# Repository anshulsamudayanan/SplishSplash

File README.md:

# SplishSplash
A graffiti inspired split keyboard with a ergonomic design
I wanted to create a mentally soothing and satifying keyboard so it will be equipped with some nice keyswitches like the holypanda and nice foam inside to get that thock
Cart pictures are attached below

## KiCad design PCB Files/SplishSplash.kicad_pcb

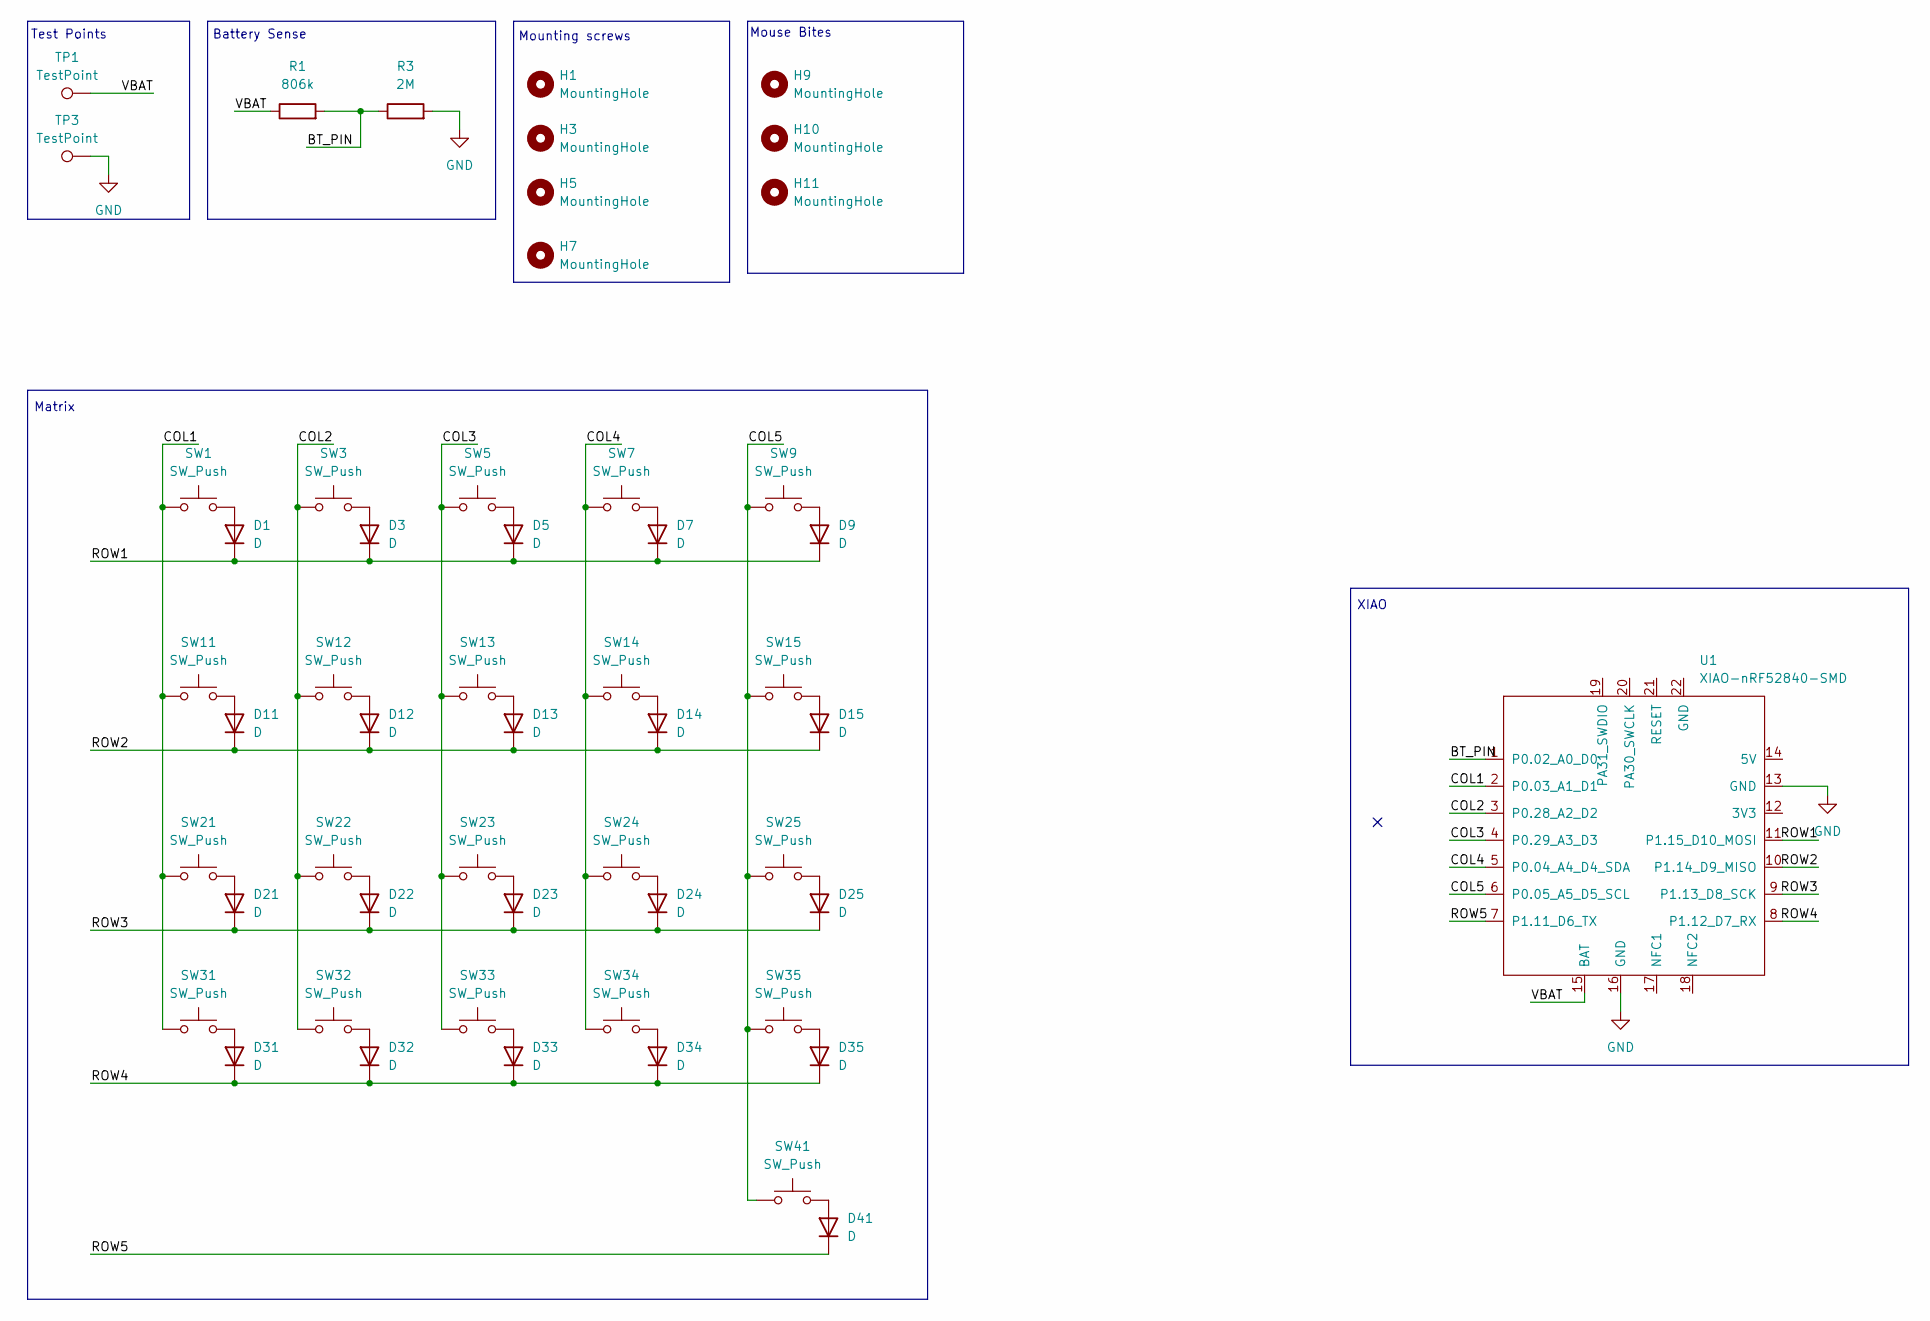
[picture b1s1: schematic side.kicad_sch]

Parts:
D1, D3, D5, D7, D9, D11, D12, D13, D14, D15, D21, D22, D23, D24, D25, D31, D32, D33, D34, D35, D41: D; D_SOD-123
H1, H3, H5, H7: MountingHole; MountingHole_2.2mm_M2
H9, H10, H11: MountingHole; mouse-bite-5mm-slot
R1: 806k; R_0805_2012Metric
R3: 2M; R_0805_2012Metric
SW1, SW3, SW5, SW7, SW9, SW11, SW12, SW13, SW14, SW15, SW21, SW22, SW23, SW24, SW25, SW31, SW32, SW33, SW34, SW35, SW41: SW_Push; SW_MX_HS_CPG151101S11_1u
TP1, TP3: TestPoint; TestPoint_Pad_D2.0mm
U1: XIAO-nRF52840-SMD; modified-XIAO-nRF52840-SMD

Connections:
/Left/BT_PIN: R1.2, R3.1, U1.1 (P0.02_A0_D0)
/Left/COL1: SW1.1, SW11.1, SW21.1, SW31.1, U1.2 (P0.03_A1_D1)
/Left/COL2: SW3.1, SW12.1, SW22.1, SW32.1, U1.3 (P0.28_A2_D2)
/Left/COL3: SW5.1, SW13.1, SW23.1, SW33.1, U1.4 (P0.29_A3_D3)
/Left/COL4: SW7.1, SW14.1, SW24.1, SW34.1, U1.5 (P0.04_A4_D4_SDA)
/Left/COL5: SW9.1, SW15.1, SW25.1, SW35.1, SW41.1, U1.6 (P0.05_A5_D5_SCL)
/Left/ROW1: D1.1 (K), D3.1 (K), D5.1 (K), D7.1 (K), D9.1 (K), U1.11 (P1.15_D10_MOSI)
/Left/ROW2: D11.1 (K), D12.1 (K), D13.1 (K), D14.1 (K), D15.1 (K), U1.10 (P1.14_D9_MISO)
/Left/ROW3: D21.1 (K), D22.1 (K), D23.1 (K), D24.1 (K), D25.1 (K), U1.9 (P1.13_D8_SCK)
/Left/ROW4: D31.1 (K), D32.1 (K), D33.1 (K), D34.1 (K), D35.1 (K), U1.8 (P1.12_D7_RX)
/Left/ROW5: D41.1 (K), U1.7 (P1.11_D6_TX)
/Left/VBAT: R1.1, TP1.1, U1.15 (BAT)
GND: R3.2, TP3.1, U1.13 (GND), U1.16 (GND); also elsewhere on the board
unnamed: D1.2 (A), SW1.2
unnamed: D3.2 (A), SW3.2
unnamed: D5.2 (A), SW5.2
unnamed: D7.2 (A), SW7.2
unnamed: D9.2 (A), SW9.2
unnamed: D11.2 (A), SW11.2
unnamed: D12.2 (A), SW12.2
unnamed: D13.2 (A), SW13.2
unnamed: D14.2 (A), SW14.2
unnamed: D15.2 (A), SW15.2
unnamed: D21.2 (A), SW21.2
unnamed: D22.2 (A), SW22.2
unnamed: D23.2 (A), SW23.2
unnamed: D24.2 (A), SW24.2
unnamed: D25.2 (A), SW25.2
unnamed: D31.2 (A), SW31.2
unnamed: D32.2 (A), SW32.2
unnamed: D33.2 (A), SW33.2
unnamed: D34.2 (A), SW34.2
unnamed: D35.2 (A), SW35.2
unnamed: D41.2 (A), SW41.2

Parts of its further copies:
D2, D4, D6, D8, D10, D16, D17, D18, D19, D20, D26, D27, D28, D29, D30, D36, D37, D38, D39, D40, D42: D; D_SOD-123
H2, H4, H6, H8: MountingHole; MountingHole_2.2mm_M2
R2: 806k; R_0805_2012Metric
R4: 2M; R_0805_2012Metric
SW2, SW4, SW6, SW8, SW10, SW16, SW17, SW18, SW19, SW20, SW26, SW27, SW28, SW29, SW30, SW36, SW37, SW38, SW39, SW40, SW42: SW_Push; SW_MX_HS_CPG151101S11_1u
TP2, TP4: TestPoint; TestPoint_Pad_D2.0mm
U2: XIAO-nRF52840-SMD; modified-XIAO-nRF52840-SMD

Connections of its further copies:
/Right/BT_PIN: R2.2, R4.1, U2.1 (P0.02_A0_D0)
/Right/COL1: SW2.1, SW16.1, SW26.1, SW36.1, U2.2 (P0.03_A1_D1)
/Right/COL2: SW4.1, SW17.1, SW27.1, SW37.1, U2.3 (P0.28_A2_D2)
/Right/COL3: SW6.1, SW18.1, SW28.1, SW38.1, U2.4 (P0.29_A3_D3)
/Right/COL4: SW8.1, SW19.1, SW29.1, SW39.1, U2.5 (P0.04_A4_D4_SDA)
/Right/COL5: SW10.1, SW20.1, SW30.1, SW40.1, SW42.1, U2.6 (P0.05_A5_D5_SCL)
/Right/ROW1: D2.1 (K), D4.1 (K), D6.1 (K), D8.1 (K), D10.1 (K), U2.11 (P1.15_D10_MOSI)
/Right/ROW2: D16.1 (K), D17.1 (K), D18.1 (K), D19.1 (K), D20.1 (K), U2.10 (P1.14_D9_MISO)
/Right/ROW3: D26.1 (K), D27.1 (K), D28.1 (K), D29.1 (K), D30.1 (K), U2.9 (P1.13_D8_SCK)
/Right/ROW4: D36.1 (K), D37.1 (K), D38.1 (K), D39.1 (K), D40.1 (K), U2.8 (P1.12_D7_RX)
/Right/ROW5: D42.1 (K), U2.7 (P1.11_D6_TX)
/Right/VBAT: R2.1, TP2.1, U2.15 (BAT)
GND: R4.2, TP4.1, U2.13 (GND), U2.16 (GND); also elsewhere on the board
unnamed: D2.2 (A), SW2.2
unnamed: D4.2 (A), SW4.2
unnamed: D6.2 (A), SW6.2
unnamed: D8.2 (A), SW8.2
unnamed: D10.2 (A), SW10.2
unnamed: D16.2 (A), SW16.2
unnamed: D17.2 (A), SW17.2
unnamed: D18.2 (A), SW18.2
unnamed: D19.2 (A), SW19.2
unnamed: D20.2 (A), SW20.2
unnamed: D26.2 (A), SW26.2
unnamed: D27.2 (A), SW27.2
unnamed: D28.2 (A), SW28.2
unnamed: D29.2 (A), SW29.2
unnamed: D30.2 (A), SW30.2
unnamed: D36.2 (A), SW36.2
unnamed: D37.2 (A), SW37.2
unnamed: D38.2 (A), SW38.2
unnamed: D39.2 (A), SW39.2
unnamed: D40.2 (A), SW40.2
unnamed: D42.2 (A), SW42.2

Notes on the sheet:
Mounting screws
Test Points
XIAO
Mouse Bites
Battery Sense
Matrix

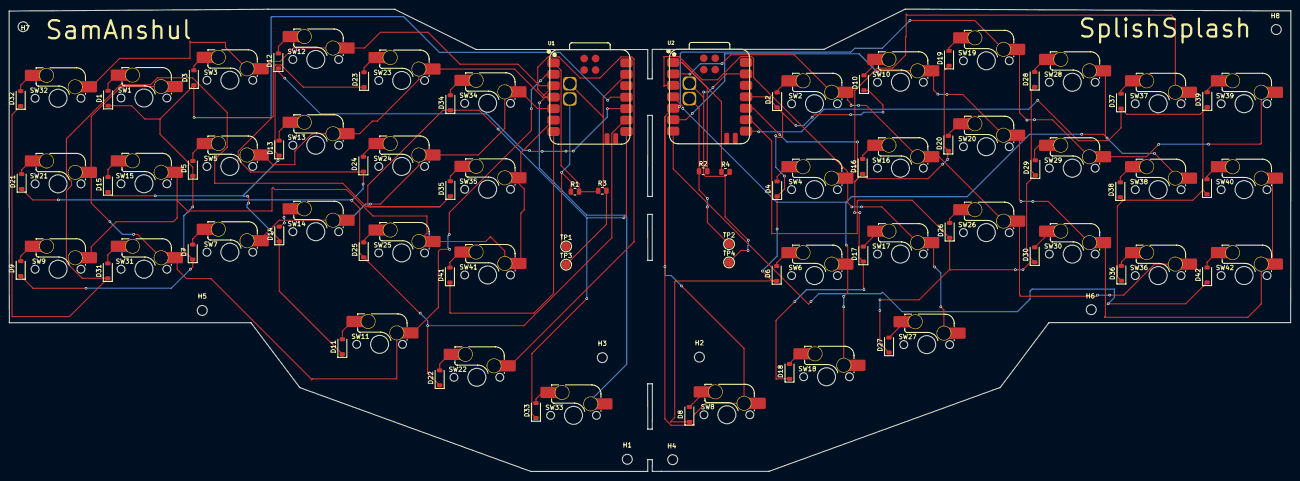
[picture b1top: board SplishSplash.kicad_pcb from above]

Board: 2 copper layers, 284.2 x 102.5 mm, 102 parts (0 on the bottom side), 67 nets.

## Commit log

2025-12-19 Create temp
2025-12-19 Enhance README with detailed keyboard description
    Expanded description of the keyboard's features and design.
